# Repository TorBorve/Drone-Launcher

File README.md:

# Drone Launcher

A platform for launching drones remotely.

## Install

### Your Computer

1. **Platformio**

    Platformio is used to compile and flash code to the teensy. The easiest way to obtain Platformio is though their vscode exstension.

2. **TeensyDuino**

    Teensy duino is used to flash code to the teensy. For instructions see here [LINK](https://www.pjrc.com/teensy/td_download.html). If you are on a standard computer with amd64 architecture the following should work:

    ```bash
    wget https://downloads.arduino.cc/arduino-1.8.15-linux64.tar.xz
    wget https://www.pjrc.com/teensy/td_154/TeensyduinoInstall.linux64
    wget https://www.pjrc.com/teensy/00-teensy.rules
    sudo cp 00-teensy.rules /etc/udev/rules.d/
    tar -xf arduino-1.8.15-linux64.tar.xz
    chmod 755 TeensyduinoInstall.linux64
    ./TeensyduinoInstall.linux64 --dir=arduino-1.8.15
    cd arduino-1.8.15/hardware/teensy/avr/cores/teensy4
    make
    ```

3. **ROS1**

    The odroid is running a ROS1 master that you can connect to. For this you will need a ROS1 version. Preferably melodic since the odroid is running that, however I have found noetic to work as well. For instructions see the offical [ROS website](http://wiki.ros.org/ROS/Installation). You also need to install these dependencies:

    ```
    sudo apt install ros-<YOUR DISTRO>-rosserial-python ros-<YOUR DISTRO>-rosserial-client
    ```

4. **Clone**

    Clone this repository into at ROS workspace ("catkin_ws"). This is bacuse this repository contains custom ROS messages that needs to be built.

5. **Static IP**

    Connect to the Drone Launcher we need to use the Rajant Radios. For this we need to specify a static ip. This IP should be in the in the form *192.168.12.69*. If it is not this specific IP you need to update the *connect_odroid_ros_master.bash* script with your ip. Depending on your OS the process will be different for achiveing this. I used ```nm-connection-editor```.

## Odroid C2

    Inside the launcher there is a Odroid C2 which needs to be configured.

1. **Ubuntu mate**
    Ubuntu mate 18.04 is used as OS. This is provided by Odroid. See instructions here: [LINK](https://wiki.odroid.com/odroid-c2/getting_started/os_installation_guide?redirect=1). You can find the os image here: [LINK](http://de.eu.odroid.in/ubuntu_18.04lts/C2/).

2. **Static IP**
    
    It is required for the Odroid to have a Static IP for the Rajant Mesh radio. If you have a screen connected you can use ```nm-connection-editor    ```. The IP should be *192.168.12.168*. If this is not the IP then several scripts might not work.

3. **ROS1**

    The odroid also needs to have ROS1 installed. If you installed ubuntu mate 18.04 you need to install ROS melodic. If you installed 20.04 it should be ROS noetic. See instructions above for how to install it. You also need to install these dependencies:

    ```
    sudo apt install ros-<YOUR DISTRO>-rosserial-python ros-<YOUR DISTRO>-rosserial-client
    ```

4. **Clone**

    The odroid also need to have this repository to work. Clone it into the foler `catkin_ws/src`. You can copy your repo over to the odroid by running: ```./scripts/copy_files_and_compile_odroid.sh```. The script will ask you for the password of the odroid a few times. The file transfer and compile will take some time.

5. **Flash code from Odroid (Optional)**

    It is possible to flash code to the Teensy from the Odroid. This makes it so that you do not have to open the launcher and connect your computer to the Teensy to flash new code. The odroid is able to pull changes from git, compile and flash the code. To do this you need to install Platformio and TeensyDuino on the Odroid as well. The prosess is similar, however we do not want the platformio exstension in vs-code. We want platformio-core only.

    You can try the *scripts/install.sh* script for installing everything on the odroid. However, keep in mind that this script is not really tested and I have had issues with installing TeensyDuino headless. Also notice that the Odroid C2 has an Aarch64 architecture and NOT am64. Therefore, the install script downloads *.linuxaarch64 and not linux64 or similar.

    ```bash
    # Make sure you are in the root directory of this repository.
    mkdir build
    ./scripts/install.sh build/
    ```
    I had two problems doing this. Firstly you need to add platformio to path. Add this line to you ~/.bashrc file: "export PATH=$PATH:/home/odroid/.platformio/penv/bin". Furthermore, I had issues installing teensyDuino. Try installing it using the gui by removing the --dir flag. Run ```./TeensyduinoInstall.linuxaarch64``` instead of ```./TeensyduinoInstall.linuxaarch64 --dir=arduino-1.8.15```.

6. **Build**
    It is necessary to build the custom ROS messages. Run:

    ```bash
    # Build catkin pkg
    catkin build
    source devel/setup.bash
    ```

4. **Drone Launcher Service**
    
    To make sure that the Odorid connects to the Teensy serial port using Rosserial on startup I have used a systemd service. The service is located in *scripts/drone_launcher.service*. We need to copy this file to the correct location and enable the service. This can be done as follows:

    ```terminal
    cp scripts/drone_launcher.service /etc/systemd/system/drone_launcher.service
    systemctl start drone_launcher.service
    systemctl enable drone_launcher.service
    ```

    You can verify that the service is running using ```systemctl status drone_launcher.service```.

    Furthermore, we should set up propper logging

## Run

### Your computer

1. **Build ROS pkg**
    We need to build our custom messages. This is done using ```catkin build``` (catkin_make should also work). Then you need to source your workspace, run: ```source devel/setup.bash``` After that we need to make header files for the messages that the Teensy will have acceess to. ```rosrun rosserial_client make_libraries <GIT_REPO_DIR>/embedded_sw/lib drone_launcher_pkg```

3. **Flash code to Teensy**
    Open a vscode window in the *embedded_ws/* folder. If platformio is installed correctly you should then see some new optinon in the bottom menu bar. After connecting the Teensy to you computer you can press the upload arrow to compile and flash code to the Teensy. See picture.

    <div align="center">
    
    <br>
    <figcaption align="center">Platformio Build and Upload</figcaption>
    </div> 

4. **Connect to Odroid**
    After you have flashed code to the Teensy and setup the Odroid we are ready to connect to it. Make sure you are connected to a Rajant mesh radio. Firstly verify that you are able to connect to the Odroid by pinging: ```ping 192.168.12.168```. If this is succesfull you can connect to the ROS master running on the odroid by sourcing the *scripts/connect_odroid_ros_master.bash*: ```source scripts/connect_odroid_ros_master.bash```. If you now run ```rostopic list``` you should see some */dronelauncher/** topics appear. 

5. **Sending ROS messages**
    You can send ROS messages to the Odroid using standard ```rostopic pub /drone_launcher/<topic> <type> <data>```. Auto complete with tab is your firend with these commands. Make sure to source the catkin workspace if you want to read the custom status messages the Odroid sends out.

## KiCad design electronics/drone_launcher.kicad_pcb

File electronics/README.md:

# Drone Launcher Electronics

This folder contains all the Schematics and PCB designs for the drone launcher. KiCAD has been used to make these. Please [download](https://www.kicad.org/download/) it to view these files. 

## Description

### Logic Connections

There are two processing units in the drone launcher: Teensy 4.1 and Odroid C2. These two communicate over serial using a micro USB cabel. The Odroid is also connected to a Rajant radio using an ethernet cabel. The Teensy is placed on a PCB which connects it to all the peripherals.

List over PCB connections:
- Limit Switches (labeled BTNS FxRx)
- Led Dtrip Drone Indicator (labeled LED DRONE)
- Arming Switch (labeled ARM SW)
- Menu Buttons (labeled MENU BTNS)
- Led Strip Battery Indicator (labeled LED BAT)
- PWM Servo Signals (labeled SERVO Fx)
- GPS connector (labeled GPS)
- LCD connector (labeled LCD)
- IMU connector (labeled IMU)

Please refere to the pcb schematic to figure out the pinouts of the different connectors.

### Power Connections

A 6s LiPo battery is used to power the system. This power goes though a 15 A fuse and a Relay. The Relay coil is connected to a emergency stop button and a key switch. If any of these are not turned no the system will not have any power. After going though the relay the power is distributed to the different devices. 

**Power Devices:**
- Teensy PCB, connect battery to XT60 plug
- Odorid, 5V@2A needed, connect micro usb plug from switching regulator
- Rajant Radio, PoE 8-60V?, connect ethernet cabel to battery voltage
- Servos, 6V, use step down regulators to provide power

    <div align="center">
        
        <br>
        <figcaption align="center">Diagram of power circuit</figcaption>
    </div>

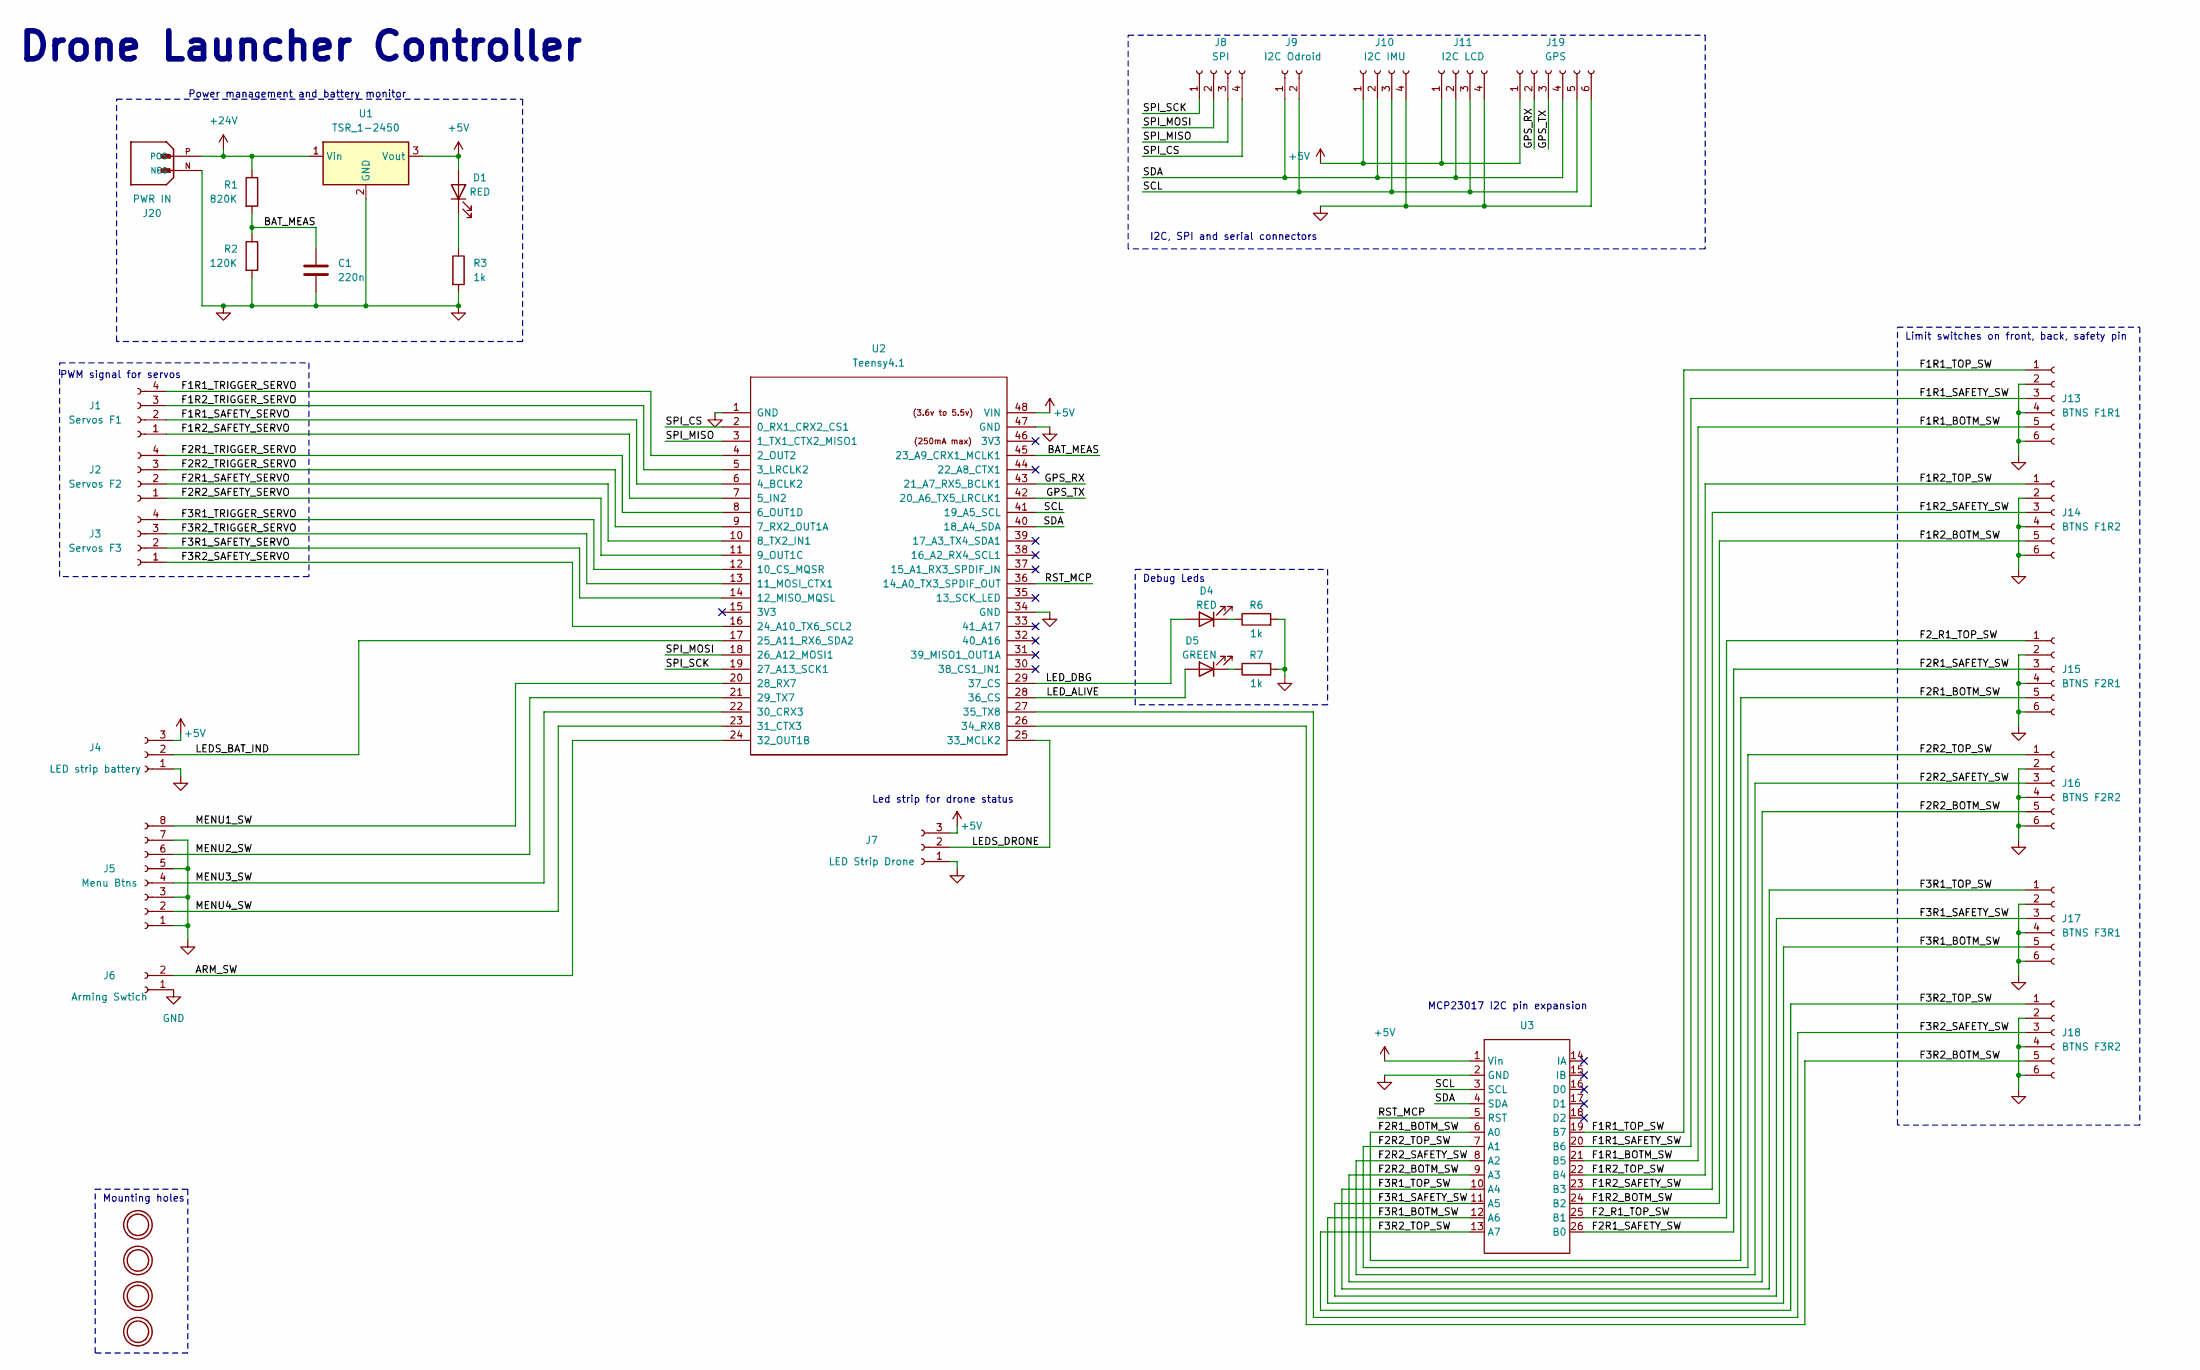
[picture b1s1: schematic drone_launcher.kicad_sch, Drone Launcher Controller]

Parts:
C1: 220n; C_1206_3216Metric
D1, D4: RED; LED_1206_3216Metric
D5: GREEN; LED_1206_3216Metric
J1: Servos F1; JST_XH_B4B-XH-A_1x04_P2.50mm_Vertical
J2: Servos F2; JST_XH_B4B-XH-A_1x04_P2.50mm_Vertical
J3: Servos F3; JST_XH_B4B-XH-A_1x04_P2.50mm_Vertical
J4: LED strip battery; JST_XH_B3B-XH-A_1x03_P2.50mm_Vertical
J5: Menu Btns; JST_XH_B8B-XH-A_1x08_P2.50mm_Vertical
J6: Arming Swtich; JST_XH_B2B-XH-A_1x02_P2.50mm_Vertical
J7: LED Strip Drone; JST_XH_B3B-XH-A_1x03_P2.50mm_Vertical
J8: SPI; JST_XH_B4B-XH-A_1x04_P2.50mm_Vertical
J9: I2C Odroid; JST_XH_B2B-XH-A_1x02_P2.50mm_Vertical
J10: I2C IMU; JST_XH_B4B-XH-A_1x04_P2.50mm_Vertical
J11: I2C LCD; JST_XH_B4B-XH-A_1x04_P2.50mm_Vertical
J13: BTNS F1R1; JST_XH_B6B-XH-A_1x06_P2.50mm_Vertical
J14: BTNS F1R2; JST_XH_B6B-XH-A_1x06_P2.50mm_Vertical
J15: BTNS F2R1; JST_XH_B6B-XH-A_1x06_P2.50mm_Vertical
J16: BTNS F2R2; JST_XH_B6B-XH-A_1x06_P2.50mm_Vertical
J17: BTNS F3R1; JST_XH_B6B-XH-A_1x06_P2.50mm_Vertical
J18: BTNS F3R2; JST_XH_B6B-XH-A_1x06_P2.50mm_Vertical
J19: GPS; JST_XH_B6B-XH-A_1x06_P2.50mm_Vertical
J20: PWR IN; AMASS_XT60-M; PARTREV V1.2
MH1, MH2, MH3, MH4: MountingHole_3.2mm_M3
R1: 820K; R_1206_3216Metric
R2: 120K; R_1206_3216Metric
R3, R6, R7: 1k; R_1206_3216Metric
U1: TSR_1-2450; Converter_DCDC_TRACO_TSR-1_THT
U2: Teensy4.1; Teensy41
U3: Adafruit_MCP23017_Breakout

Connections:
+5V: D1.2 (A), J4.3, J7.3, J10.1, J11.1, J19.1, U1.3 (Vout), U2.48 (VIN), U3.1 (Vin)
+24V: J20.P (POS), R1.1, U1.1 (Vin)
/ARM_SW: J6.2, U2.24 (32_OUT1B)
/BAT_MEAS: C1.1, R1.2, R2.1, U2.45 (23_A9_CRX1_MCLK1)
/F1R1_BOTM_SW: J13.5, U3.21 (B5)
/F1R1_SAFETY_SERVO: J1.2, U2.6 (4_BCLK2)
/F1R1_SAFETY_SW: J13.3, U3.20 (B6)
/F1R1_TOP_SW: J13.1, U3.19 (B7)
/F1R1_TRIGGER_SERVO: J1.4, U2.4 (2_OUT2)
/F1R2_BOTM_SW: J14.5, U3.24 (B2)
/F1R2_SAFETY_SERVO: J1.1, U2.7 (5_IN2)
/F1R2_SAFETY_SW: J14.3, U3.23 (B3)
/F1R2_TOP_SW: J14.1, U3.22 (B4)
/F1R2_TRIGGER_SERVO: J1.3, U2.5 (3_LRCLK2)
/F2R1_BOTM_SW: J15.5, U3.6 (A0)
/F2R1_SAFETY_SERVO: J2.2, U2.10 (8_TX2_IN1)
/F2R1_SAFETY_SW: J15.3, U3.26 (B0)
/F2R1_TRIGGER_SERVO: J2.4, U2.8 (6_OUT1D)
/F2R2_BOTM_SW: J16.5, U3.9 (A3)
/F2R2_SAFETY_SERVO: J2.1, U2.11 (9_OUT1C)
/F2R2_SAFETY_SW: J16.3, U3.8 (A2)
/F2R2_TOP_SW: J16.1, U3.7 (A1)
/F2R2_TRIGGER_SERVO: J2.3, U2.9 (7_RX2_OUT1A)
/F2_R1_TOP_SW: J15.1, U3.25 (B1)
/F3R1_BOTM_SW: J17.5, U3.12 (A6)
/F3R1_SAFETY_SERVO: J3.2, U2.14 (12_MISO_MQSL)
/F3R1_SAFETY_SW: J17.3, U3.11 (A5)
/F3R1_TOP_SW: J17.1, U3.10 (A4)
/F3R1_TRIGGER_SERVO: J3.4, U2.12 (10_CS_MQSR)
/F3R2_BOTM_SW: J18.5, U2.26 (34_RX8)
/F3R2_SAFETY_SERVO: J3.1, U2.16 (24_A10_TX6_SCL2)
/F3R2_SAFETY_SW: J18.3, U2.27 (35_TX8)
/F3R2_TOP_SW: J18.1, U3.13 (A7)
/F3R2_TRIGGER_SERVO: J3.3, U2.13 (11_MOSI_CTX1)
/GPS_RX: J19.2, U2.43 (21_A7_RX5_BCLK1)
/GPS_TX: J19.3, U2.42 (20_A6_TX5_LRCLK1)
/LEDS_BAT_IND: J4.2, U2.17 (25_A11_RX6_SDA2)
/LEDS_DRONE: J7.2, U2.25 (33_MCLK2)
/LED_ALIVE: D5.2 (A), U2.28 (36_CS)
/LED_DBG: D4.2 (A), U2.29 (37_CS)
/MENU1_SW: J5.8, U2.20 (28_RX7)
/MENU2_SW: J5.6, U2.21 (29_TX7)
/MENU3_SW: J5.4, U2.22 (30_CRX3)
/MENU4_SW: J5.2, U2.23 (31_CTX3)
/RST_MCP: U2.36 (14_A0_TX3_SPDIF_OUT), U3.5 (RST)
/SCL: J9.2, J10.3, J11.3, J19.5, U2.41 (19_A5_SCL), U3.3 (SCL)
/SDA: J9.1, J10.2, J11.2, J19.4, U2.40 (18_A4_SDA), U3.4 (SDA)
/SPI_CS: J8.4, U2.2 (0_RX1_CRX2_CS1)
/SPI_MISO: J8.3, U2.3 (1_TX1_CTX2_MISO1)
/SPI_MOSI: J8.2, U2.18 (26_A12_MOSI1)
/SPI_SCK: J8.1, U2.19 (27_A13_SCK1)
GND: C1.2, J4.1, J5.1, J5.3, J5.5, J5.7, J6.1, J7.1, J10.4, J11.4, J13.2, J13.4, J13.6, J14.2, J14.4, J14.6, J15.2, J15.4, J15.6, J16.2, J16.4, J16.6, J17.2, J17.4, J17.6, J18.2, J18.4, J18.6, J19.6, J20.N (NEG), R2.2, R3.2, R6.2, R7.2, U1.2 (GND), U2.1 (GND), U2.34 (GND), U2.47 (GND), U3.2 (GND)
unnamed: D1.1 (K), R3.1
unnamed: D4.1 (K), R6.1
unnamed: D5.1 (K), R7.1

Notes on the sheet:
PWM signal for servos
Drone Launcher Controller
Mounting holes
Led strip for drone status
I2C, SPI and serial connectors
Power management and battery monitor
Limit switches on front, back, safety pin
Debug Leds
MCP23017 I2C pin expansion

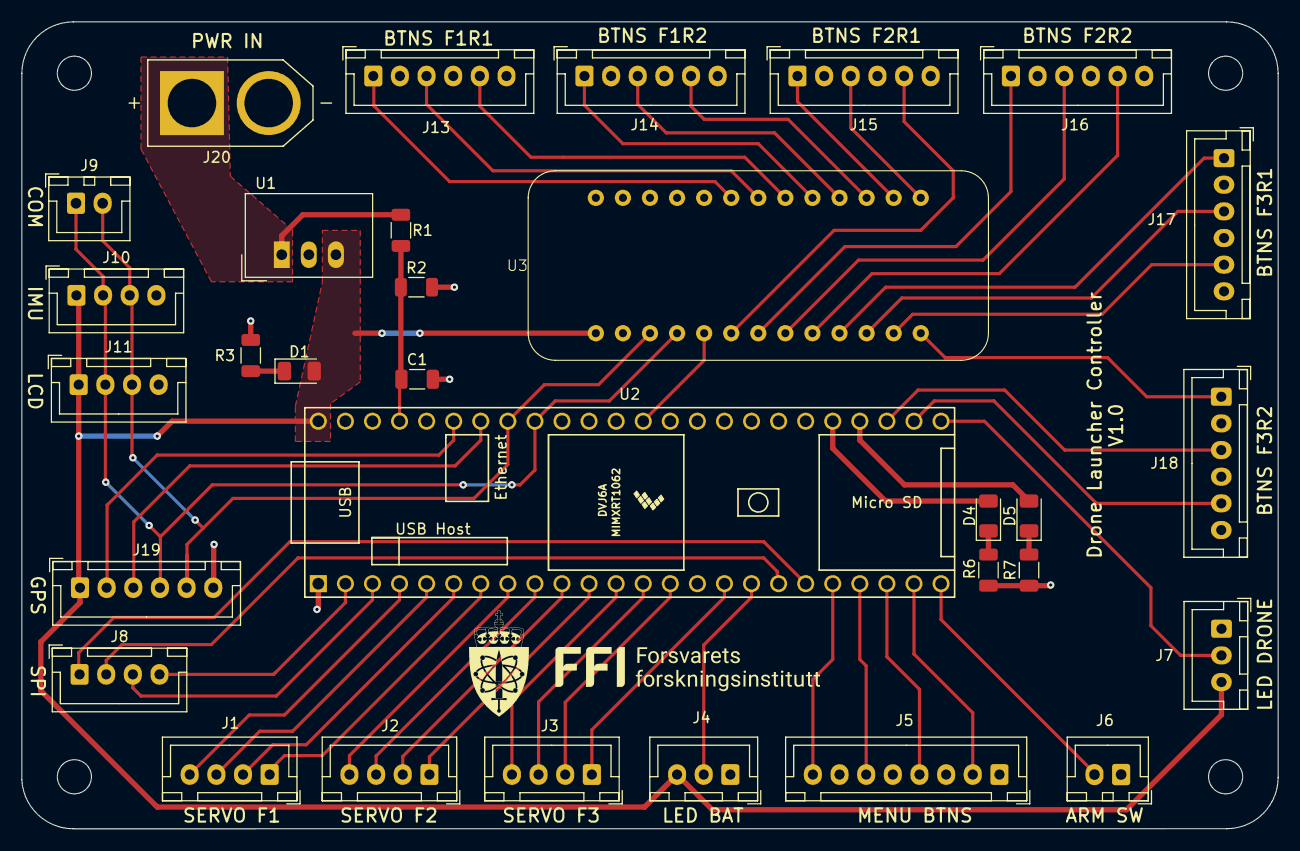
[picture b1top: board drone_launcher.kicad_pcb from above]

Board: 2 copper layers, 117.9 x 75.7 mm, 35 parts (0 on the bottom side), 55 nets.

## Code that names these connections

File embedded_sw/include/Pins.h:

#pragma once

#include <Adafruit_MCP23X17.h>

///////////////////////////
// MCP23X17 Pin extensions
///////////////////////////

namespace DroneLauncher {

namespace pins {

extern Adafruit_MCP23X17 mcp;

void setup();

}  // namespace pins

#define PINS_MCP_OFFSET 64

#define PINS_MCP_ADDR 0x21

#define pinModeExt(pin, mode) (pin >= PINS_MCP_OFFSET) ? pins::mcp.pinMode(pin - PINS_MCP_OFFSET, mode) : pinMode(pin, mode)

#define digitalWriteExt(pin, value) (pin >= PINS_MCP_OFFSET) ? pins::mcp.digitalWrite(pin - PINS_MCP_OFFSET, value) : digitalWrite(pin, value)

#define digitalReadExt(pin) (pin >= PINS_MCP_OFFSET ? pins::mcp.digitalRead(pin - PINS_MCP_OFFSET) : digitalRead(pin))

///////////////////////////
// Pin Mapping
///////////////////////////

#define PIN_MY_SPI_CS 0
#define PIN_MY_SPI_MISO 1
#define PIN_F1R1_TRIGGER_SERVO 2
#define PIN_F1R2_TRIGGER_SERVO 3
#define PIN_F1R1_SAFETY_SERVO 4
#define PIN_F1R2_SAFETY_SERVO 5
#define PIN_F2R1_TRIGGER_SERVO 6
#define PIN_F2R2_TRIGGER_SERVO 7
#define PIN_F2R1_SAFETY_SERVO 8
#define PIN_F2R2_SAFETY_SERVO 9
#define PIN_F3R1_TRIGGER_SERVO 10
#define PIN_F3R2_TRIGGER_SERVO 11
#define PIN_F3R1_SAFETY_SERVO 12
#define PIN_F3R2_SAFETY_SERVO 24
#define PIN_BAT_LEDS 25
#define PIN_MY_SPI_MOSI 26
#define PIN_MY_SPI_SCK 27
#define PIN_MENU_BACK 28
#define PIN_MENU_UP 29
#define PIN_MENU_DOWN 30
#define PIN_MENU_SELECT 31
#define PIN_ARM_SWITCH 32

#define PIN_BAT_MEAS 23
#define PIN_GPS_RX 21
#define PIN_GPS_TX 20
#define PIN_SCL 19
#define PIN_SDA 18
#define PIN_RESET_MCP 14
#define PIN_LED_DBG 37
#define PIN_LED_ALIVE 36
#define PIN_F3R2_SAFETY_SWITCH 35
#define PIN_F3R2_REAR_SWITCH 34
#define PIN_DRONE_LEDS 33

#define PIN_F2R1_REAR_SWITCH (0 + PINS_MCP_OFFSET)
#define PIN_F2R2_FRONT_SWITCH (1 + PINS_MCP_OFFSET)
#define PIN_F2R2_SAFETY_SWITCH (2 + PINS_MCP_OFFSET)
#define PIN_F2R2_REAR_SWITCH (3 + PINS_MCP_OFFSET)
#define PIN_F3R1_FRONT_SWITCH (4 + PINS_MCP_OFFSET)
#define PIN_F3R1_SAFETY_SWITCH (5 + PINS_MCP_OFFSET)
#define PIN_F3R1_REAR_SWITCH (6 + PINS_MCP_OFFSET)
#define PIN_F3R2_FRONT_SWITCH (7 + PINS_MCP_OFFSET)
#define PIN_F2R1_SAFETY_SWITCH (8 + PINS_MCP_OFFSET)
#define PIN_F2R1_FRONT_SWITCH (9 + PINS_MCP_OFFSET)
#define PIN_F1R2_REAR_SWITCH (10 + PINS_MCP_OFFSET)
#define PIN_F1R2_SAFETY_SWITCH (11 + PINS_MCP_OFFSET)
#define PIN_F1R2_FRONT_SWITCH (12 + PINS_MCP_OFFSET)
#define PIN_F1R1_REAR_SWITCH (13 + PINS_MCP_OFFSET)
#define PIN_F1R1_SAFETY_SWITCH (14 + PINS_MCP_OFFSET)
#define PIN_F1R1_FRONT_SWITCH (15 + PINS_MCP_OFFSET)

}  // namespace DroneLauncher

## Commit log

2023-06-27 inital commit
2023-06-27 simple button class
2023-06-27 started on launch unit class
2023-06-27 testing btn triggered launch
2023-07-04 testing stuff
2023-07-07 added electrical files
2023-07-07 moved embedded sw files
2023-07-07 moved files
2023-07-07 added mcp23017 footprint and 3D model
2023-07-07 backup files
2023-07-07 added labels and initial pcb layout
2023-07-10 fixed pin numbering
2023-07-10 added xt60 lib
2023-07-10 improved routing and new footprints
2023-07-11 updated libs aand more
2023-07-11 version 1.0 pcb
2023-07-11 added gbr files
2023-07-13 using teensy 4.1
2023-07-13 updated button and switch class
2023-07-13 threads and more for launch unit
2023-07-14 added led classes
2023-07-14 Leds synchronized blinking
2023-07-14 first version launch unit
2023-07-14 testing launch unit
2023-07-14 added use of MCP expansion board
2023-07-14 added init functions to avoid issues with mcp pins
2023-07-14 fixed included multiple error
2023-07-14 bug, bias not used
2023-07-14 intial work on launchSystem class
2023-07-18 started on lcd menu
2023-07-18 Added battery monitor files to monitor battery
2023-07-18 added all pin mappings
2023-07-18 made methods private
2023-07-18 using pin mappings and leds
2023-07-18 initial ros interface
2023-07-18 cleaning up main
2023-07-19 added log macro
2023-07-19 updated gitignore
2023-07-19 fixed redef of pins
2023-07-19 more logging
2023-07-19 added custom messages
2023-07-19 Implemented battery monitoring class
2023-07-19 Added accurate battery voltage range
2023-07-19 implemented status publisher
2023-07-19 fixed bugs and code quality
2023-07-19 slower updates
2023-07-19 removed logging
2023-07-20 first version simple menu
2023-07-20 include menu in main
2023-07-20 logging formatting enable
2023-07-20 menu call launch system
2023-07-20 using battery monitor
2023-07-20 Implemented GPS class
2023-07-20 Small Formatting Changes
2023-07-20 scripts for installing and running on host machine
2023-08-02 testing and fixing bugs
2023-08-02 added script for connecting to odroid ROS master
2023-08-02 info install and run
2023-08-02 readme
2023-08-03 safety delay fire
2023-08-03 shit fix mirrored servos
2023-08-03 fixed unload bug
2023-08-03 fixed retracting servo on startup bug
2023-08-03 removed timout on screen
2023-08-04 fixed range of IDs available
2023-08-04 name change
2023-08-04 rename and launch file
2023-08-04 changed name
2023-08-04 documenting electrical stuff
2023-08-04 started on IMU
2023-08-04 documenting a bit code
2023-08-04 merged files and name change
2023-08-04 old file
2023-08-04 formatting
2023-08-04 cleaning up and simplifying
2023-08-04 GPS and orientation in status
2023-08-07 fixed GPS fix and correct serial port
2023-08-07 DroneLauncher namespace
2023-08-07 some comments and cleaning up
2023-08-07 formatting files
2023-08-07 manual control message
2023-08-07 added manual control topic and control
2023-08-07 fixed #11
2023-08-07 fixes #1 (to some degree)
2023-08-07 fixes #15
2023-08-08 fixed small bugs and testing
2023-08-09 ros documentation
2023-08-09 added info ip address and source devel
2023-08-09 sync fire several drones
2023-08-09 fixes #18
2023-08-09 removed check on load
2023-08-09 updating scripts
